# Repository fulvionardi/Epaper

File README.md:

# Waveshare 3.6inch e-Paper HAT+ Schematic Replication

## Overview

This project is a replication of the **Waveshare 3.6inch e-Paper HAT+** schematics, originally documented in `3.6inch_e-Paper_HAT+_Schematics.pdf`. The goal is to recreate the schematic faithfully in **KiCad** for learning, modification, or custom PCB development purposes.

The original hardware is a 600×400 pixel e-paper display HAT designed for the Raspberry Pi/ESP32, manufactured by Waveshare.

📄 **[View Original Schematic (PDF)](./3.6inch_e-Paper_HAT+_Schematic.pdf)**

---

## Source Reference

- **Original schematic:** `3.6inch_e-Paper_HAT+_Schematics.pdf`
- **Source link:** https://www.waveshare.com/wiki/3.6inch_e-Paper_HAT%2B_(E)_Manual?srsltid=AfmBOorWlnluAFoRzEwT3edqMAU8t9G03QhICEiQ9qgBs1PhjLsAxZD9#Precautions
- **Manufacturer:** Waveshare
- **Product:** 3.6inch e-Paper HAT+ (600×400 pixels)
- **Interface:** SPI (3-line or 4-line, selectable via BS0/BS1)

---

## Project Structure

```
├── .gitignore
├── README.md
├── 3.6inch_e-Paper_HAT+_Schematic.pdf  # Original Waveshare reference schematic
├── Hat_Eink_Esp32.bak                  # KiCad schematic backup
├── Hat_Eink_Esp32.kicad_sym            # Custom symbol library
├── Schematics.kicad_pcb                # PCB layout file
├── Schematics.kicad_prl                # Project local settings
├── Schematics.kicad_pro                # KiCad project file
├── Schematics.kicad_sch                # Main schematic file
└── coil_maker.py                       # Helper script
```

---

## TODO

- [ ] **Test on real hardware** — validate the completed board against a physical microprocessor and e-paper display to confirm correct operation
- [ ] **Review unnecessary components** — some components from the original Waveshare driver circuit may not be needed depending on the target use case; evaluate what can be simplified or removed

---

## License

This replication is for educational and personal use only. All original design rights belong to **Waveshare Electronics**.

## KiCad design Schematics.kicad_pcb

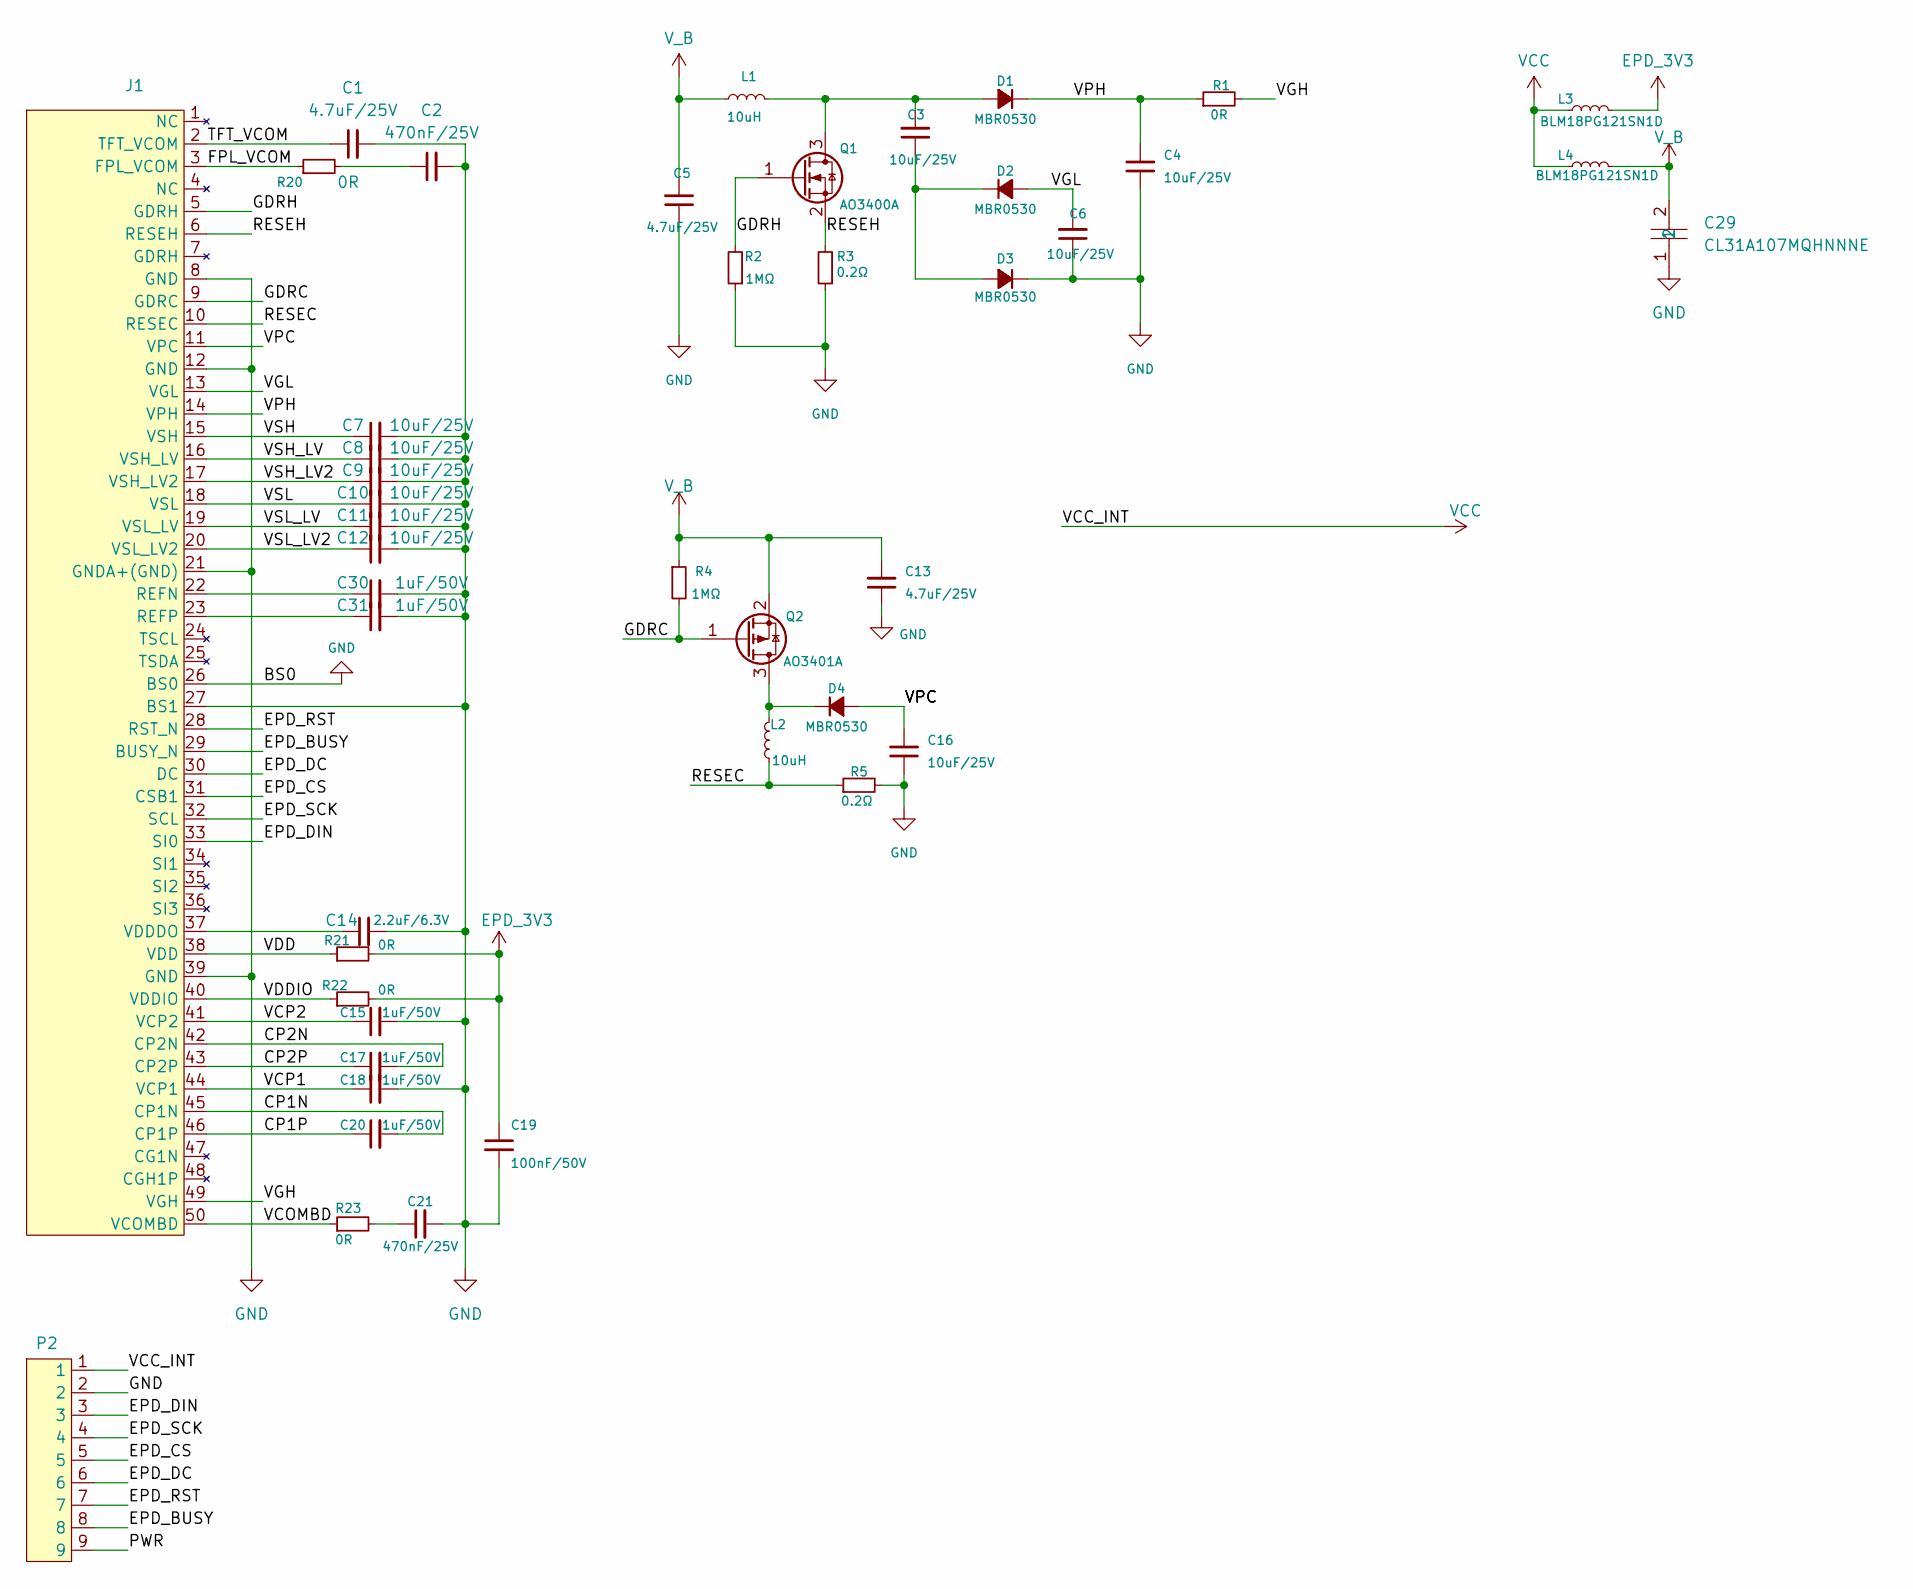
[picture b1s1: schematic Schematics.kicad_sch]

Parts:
C1, C5, C13: 4.7uF/25V; C_0805_2012Metric
C2, C21: 470nF/25V; C_0603_1608Metric
C3, C4, C6, C7, C8, C9, C10, C11, C12, C16: 10uF/25V; C_0603_1608Metric
C14: 2.2uF/6.3V; C_0402_1005Metric
C15, C17, C18, C20, C30, C31: 1uF/50V; C_0603_1608Metric
C19: 100nF/50V; C_0603_1608Metric
C29: CL31A107MQHNNNE; C1206; MPN CL31A107MQHNNNE; LCSC Part C15008
D1, D2, D3, D4: MBR0530; SOD-123_L2.7-W1.6-LS3.7-RD-1
J1: FPC-SMD_50P-P0.50_FPC0.5-WFB11-50P111-H20
L1, L2: 10uH; L0805
L3, L4: BLM18PG121SN1D; L0603
P2: CONN-SMD_9P-P1.25_MOLEX_532610971
Q1: AO3400A; SOT-23-3_L2.9-W1.3-P1.90-LS2.4-BR
Q2: AO3401A; SOT-23-3_L2.9-W1.3-P1.90-LS2.4-BR
R1, R20, R21, R22, R23: 0R; R_0603_1608Metric
R2, R4: 1MΩ; R_0603_1608Metric
R3, R5: 0.2Ω; R_0603_1608Metric

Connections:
/CP1N: C20.2, J1.45 (CP1N)
/CP1P: C20.1, J1.46 (CP1P)
/CP2N: C17.2, J1.42 (CP2N)
/CP2P: C17.1, J1.43 (CP2P)
/EPD_BUSY: J1.29 (BUSY_N), P2.8
/EPD_CS: J1.31 (CSB1), P2.5
/EPD_DC: J1.30 (DC), P2.6
/EPD_DIN: J1.33 (SI0), P2.3
/EPD_RST: J1.28 (RST_N), P2.7
/EPD_SCK: J1.32 (SCL), P2.4
/FPL_VCOM: J1.3 (FPL_VCOM), R20.1
/GDRC: J1.9 (GDRC), Q2.1 (G), R4.2
/GDRH: J1.5 (GDRH), Q1.1 (G), R2.2
/PWR: P2.9
/RESEC: J1.10 (RESEC), L2.1, R5.1
/RESEH: J1.6 (RESEH), Q1.2 (S), R3.2
/TFT_VCOM: C1.1, J1.2 (TFT_VCOM)
/VCOMBD: J1.50 (VCOMBD), R23.1
/VCP1: C18.1, J1.44 (VCP1)
/VCP2: C15.1, J1.41 (VCP2)
/VDD: J1.38 (VDD), R21.1
/VDDIO: J1.40 (VDDIO), R22.1
/VGH: J1.49 (VGH), R1.2
/VGL: C6.2, D2.2 (A), J1.13 (VGL)
/VPC: C16.2, D4.2 (A), J1.11 (VPC)
/VPH: C4.2, D1.1 (K), J1.14 (VPH), R1.1
/VSH: C7.1, J1.15 (VSH)
/VSH_LV: C8.1, J1.16 (VSH_LV)
/VSH_LV2: C9.1, J1.17 (VSH_LV2)
/VSL: C10.1, J1.18 (VSL)
/VSL_LV: C11.1, J1.19 (VSL_LV)
/VSL_LV2: C12.1, J1.20 (VSL_LV2)
EPD_3V3: C19.1, L3.2, R21.2, R22.2
GND: C1.2, C2.2, C4.1, C5.1, C6.1, C7.2, C8.2, C9.2, C10.2, C11.2, C12.2, C13.1, C14.2, C15.2, C16.1, C18.2, C19.2, C21.2, C29.1, C30.2, C31.2, D3.1 (K), J1.8 (GND), J1.12 (GND), J1.21 (GNDA+(GND)), J1.26 (BS0), J1.27 (BS1), J1.39 (GND), P2.2, R2.1, R3.1, R5.2; also elsewhere on the board
unnamed: C2.1, R20.2
unnamed: C21.1, R23.2
unnamed: C3.2, D1.2 (A), L1.2, Q1.3 (D)
unnamed: C3.1, D2.1 (K), D3.2 (A)
unnamed: D4.1 (K), L2.2, Q2.3 (D)
unnamed: C30.1, J1.22 (REFN)
unnamed: C31.1, J1.23 (REFP)
unnamed: C14.1, J1.37 (VDDDO)
VCC: L3.1, L4.1, P2.1; also elsewhere on the board
V_B: C5.2, C13.2, C29.2, L1.1, L4.2, Q2.2 (S), R4.1

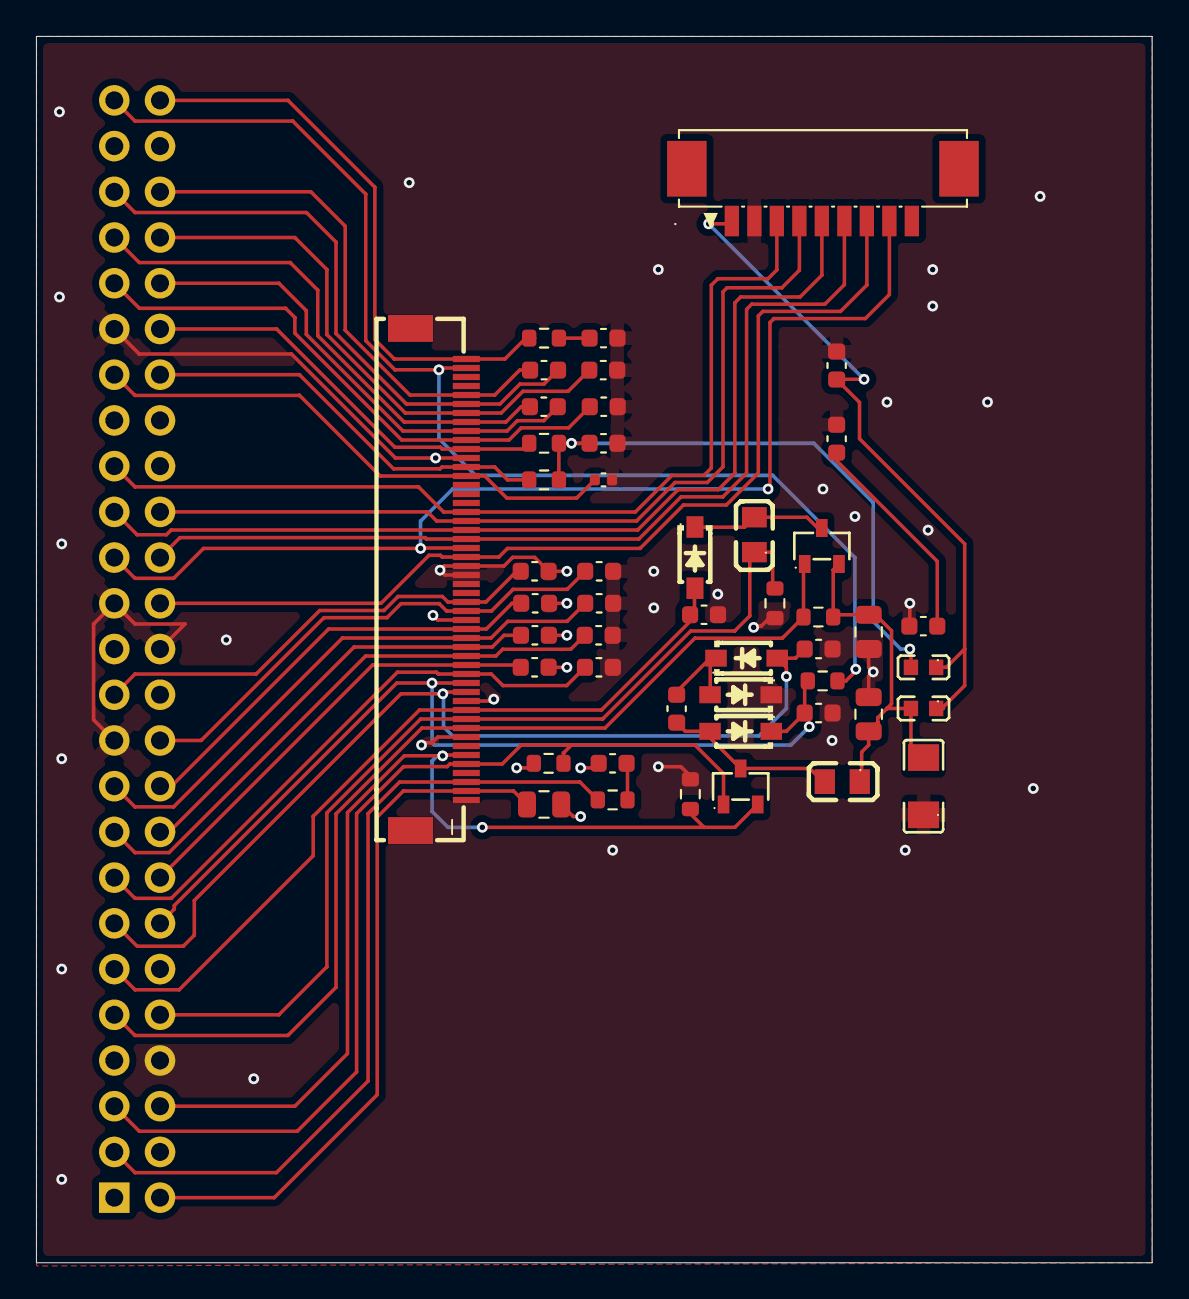
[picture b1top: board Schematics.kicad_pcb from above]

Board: 2 copper layers, 62.0 x 68.1 mm, 48 parts (0 on the bottom side), 44 nets.

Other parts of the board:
C24, C25, C27: 1uF/50V; C_0603_1608Metric

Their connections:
3V3_OUT: C24.1, C27.2
GND: C24.2, C25.2, C27.1; also elsewhere on the board
VCC: C25.1; also elsewhere on the board

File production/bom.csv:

Designator,Footprint,Quantity,Value,LCSC Part #
"C1, C13, C5",0805,3,4.7uF/25V,C1779
"C10, C11, C12, C16, C3, C4, C6, C7, C8, C9",0603,10,10uF/25V,C96446
C14,0402,1,2.2uF/6.3V,C12530
"C15, C17, C18, C20, C24, C25, C27, C30, C31",0603,9,1uF/50V,C15849
C19,0603,1,100nF/50V,C14663
"C2, C21",0603,2,470nF/25V,C1623
"D1, D2, D3, D4",SOD-123_L2.7-W1.6-LS3.7-RD-1,4,MBR0530,C8598
J1,FPC-SMD_50P-P0.50_FPC0.5-WFB11-50P111-H20,1,~,C42407956
"L1, L2",L0805,2,10uH,C281097
"L3, L4",L0603,2,BLM18PG121SN1D,C14709
P2,CONN-SMD_9P-P1.25_MOLEX_532610971,1,~,C379029
Q1,SOT-23-3_L2.9-W1.3-P1.90-LS2.4-BR,1,AO3400A,C20917
Q2,SOT-23-3_L2.9-W1.3-P1.90-LS2.4-BR,1,AO3401A,C15127
R1,0603,1,0R,
"R2, R4",0603,2,1MΩ,C22935
"R20, R21, R22, R23",0603,4,0R,C21189
"R3, R5",0805,2,0.22Ω,C17557

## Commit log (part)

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2026-05-16 added README file
2026-05-16 Fixed from 4 inches display to 3.6 inches
2026-05-16 -fixed file structure on the README
2026-05-16 improve README by removing AI clutter text and adding images
2026-05-16 added image for the readme
2026-05-16 fixed images
2026-05-16 added png image
2026-05-17 added raspberry pi footprint and README
2026-05-17 added few footprints
2026-05-27 Assign footprints to all components and started pcb layout and connessions
2026-06-07 completed PCB Layout
2026-06-07 appended PCB preview image in the readme
2026-06-13 fixed minor connection mistakes/errors, and added BOM and POS files
2026-06-13 removed solder paste layer
2026-06-13 made changes to simplify the board
2026-06-13 updated board by removing unnecessary elements
2026-06-13 added missing connection
2026-06-14 completed minimalist schematics and PCB of epaper
